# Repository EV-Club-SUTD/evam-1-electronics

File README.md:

# EVAM 1 Electronics Modules

> Design and manufacturing files for the EVAM 1's electrical and CAN bus system

- [x] 🏎️ Automotive Hardware
- [ ] 🛞 Automotive Software
- [ ] 🖥️ Supporting Software and Simulations
- [ ] 📚 Code Library
- [ ] 🛠 Helper Script
- [x] 📖 Documentation / Datasheets
- [ ] ❓ Miscellaneous / Uncategorized

This repository contains the hardware design and manufacturing files for the EVAM 1's electrical system.  

## Directories

* `CANBus 2/Design` - Design files in KiCAD format
    * `/APPS` - Throttle position sensor PCB
    * `/BMS` - Battery Management System PCB
    * `/ECU` - Engine Control Unit PCB
    * `/HUD` - Heads up Display PCB
    * `/MCU_Double` - Motor Control Unit, double motor (for front motors)
    * `/MCU_Single` - Motor Control Unit, single motor (for rear motors)
    * `/SAS` - Steering Angle Sensor, originally meant for torque vectoring. Currently not used
* `CANBus 2/Manufacturing` - Manufacturing files (BOM, placement, and Gerbers)
* `CANBus 2/Electrical Layout` - Electrical layout design files, including block diagrams, to describe the high level overview of the entire electrical system
* `CANBus 2/Harness` - Cable harness design files and pictorial diagrams
* `Datasheets` - All the datasheets for the various components employed in the vehicle

## Documentation

Please refer to EVAM internal OneDrive for further documentation, including specific datasheets on the electrical system components

## Caveats

No known caveats yet

## Known issues

No known issues yet

## Contributing

If you encounter any issues with this repository, please do not hesitate to open an issue.

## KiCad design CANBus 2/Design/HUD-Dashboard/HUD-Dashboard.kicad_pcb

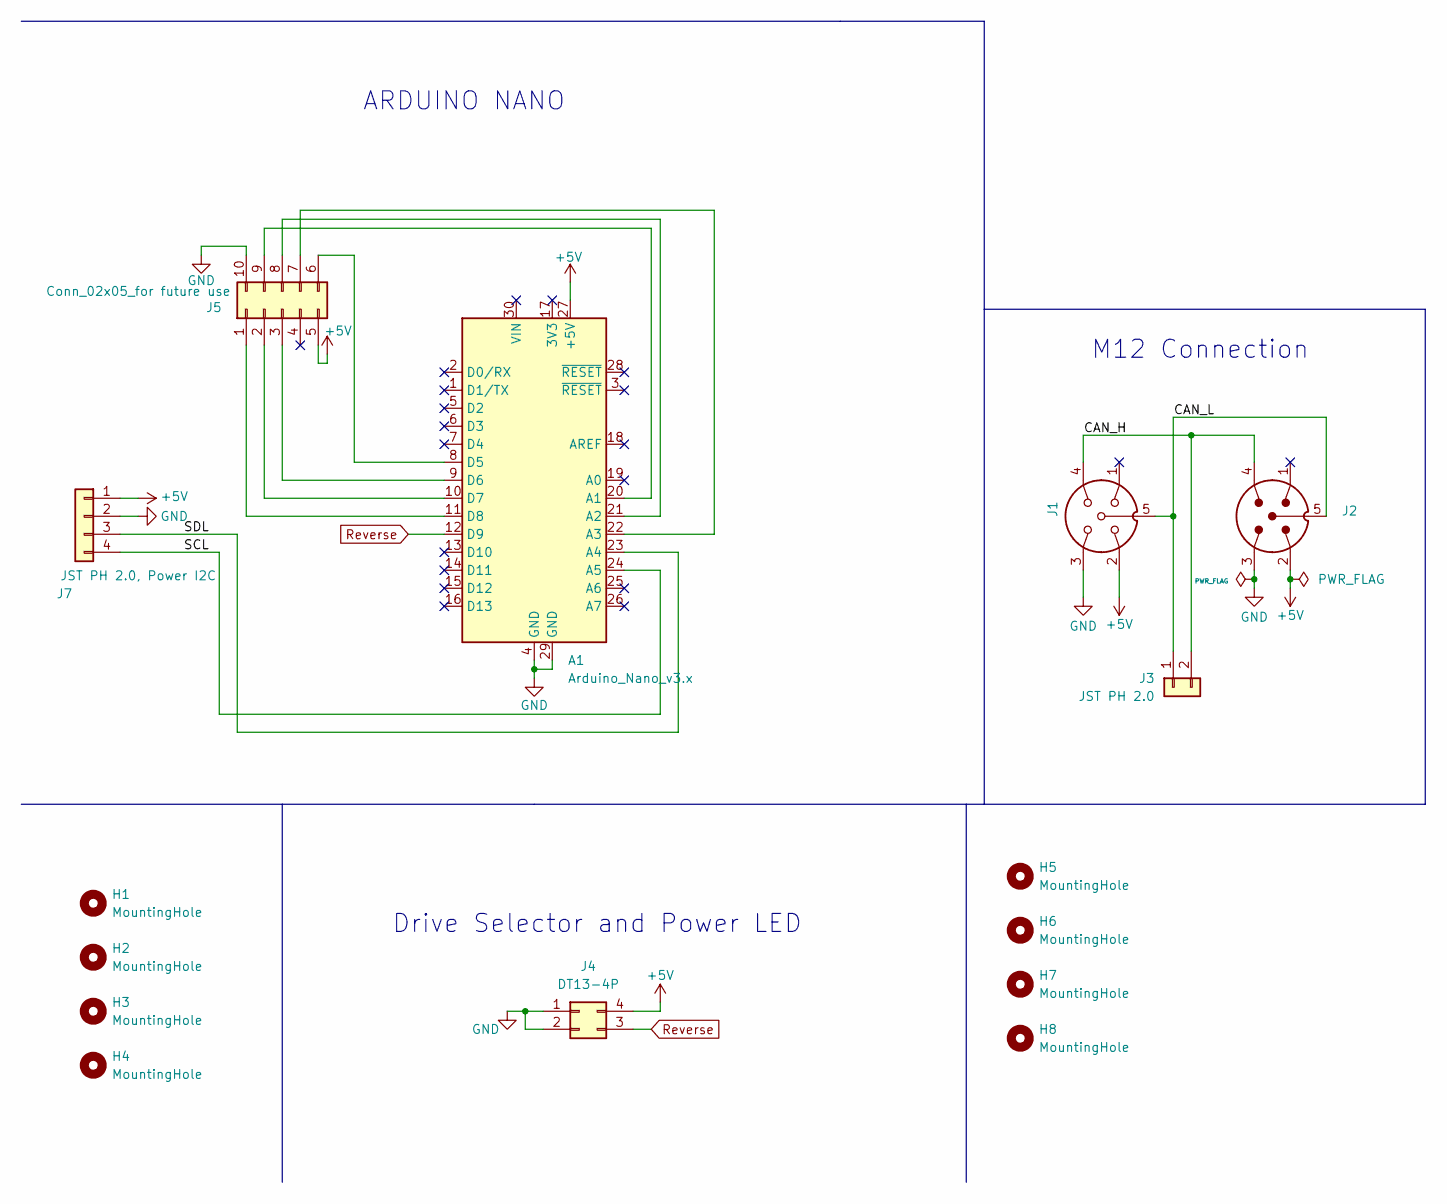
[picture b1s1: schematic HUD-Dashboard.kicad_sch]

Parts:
A1: Arduino_Nano_v3.x; Arduino_Nano
H1, H2, H3, H4, H5, H6, H7, H8: MountingHole; MountingHole_3.2mm_M3_ISO14580
J1: T4145015051-001; M12-S5A-GPL; PARTREV A
J2: TE_T4144015051-000; M12-P5A-GPL; PARTREV A
J3: JST PH 2.0; CONN-TH_2P-P2.00_ZX-HY2.0-2PZZ
J4: DT13-4P; TE_DT13-4P
J5: Conn_02x05_for future use; PinSocket_2x05_P2.54mm_Vertical
J7: JST PH 2.0, Power I2C; CONN-TH_4P-P2.00_ZX-HY2.0-4PZZ

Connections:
+5V: A1.27 (+5V), J1.2, J2.2, J4.4, J5.5, J7.1
/CAN_H: J1.4, J2.4, J3.2
/CAN_L: J1.5, J2.5, J3.1
/SCL: A1.24 (A5), J7.4
/SDL: A1.23 (A4), J7.3
GND: A1.4 (GND), A1.29 (GND), J1.3, J2.3, J4.1, J4.2, J5.10, J7.2
unnamed: A1.20 (A1), J5.9
unnamed: A1.21 (A2), J5.8
unnamed: A1.22 (A3), J5.7
unnamed: A1.8 (D5), J5.6
unnamed: A1.9 (D6), J5.3
unnamed: A1.10 (D7), J5.2
unnamed: A1.11 (D8), J5.1
Reverse: A1.12 (D9), J4.3

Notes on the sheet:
Drive Selector and Power LED
ARDUINO NANO
M12 Connection

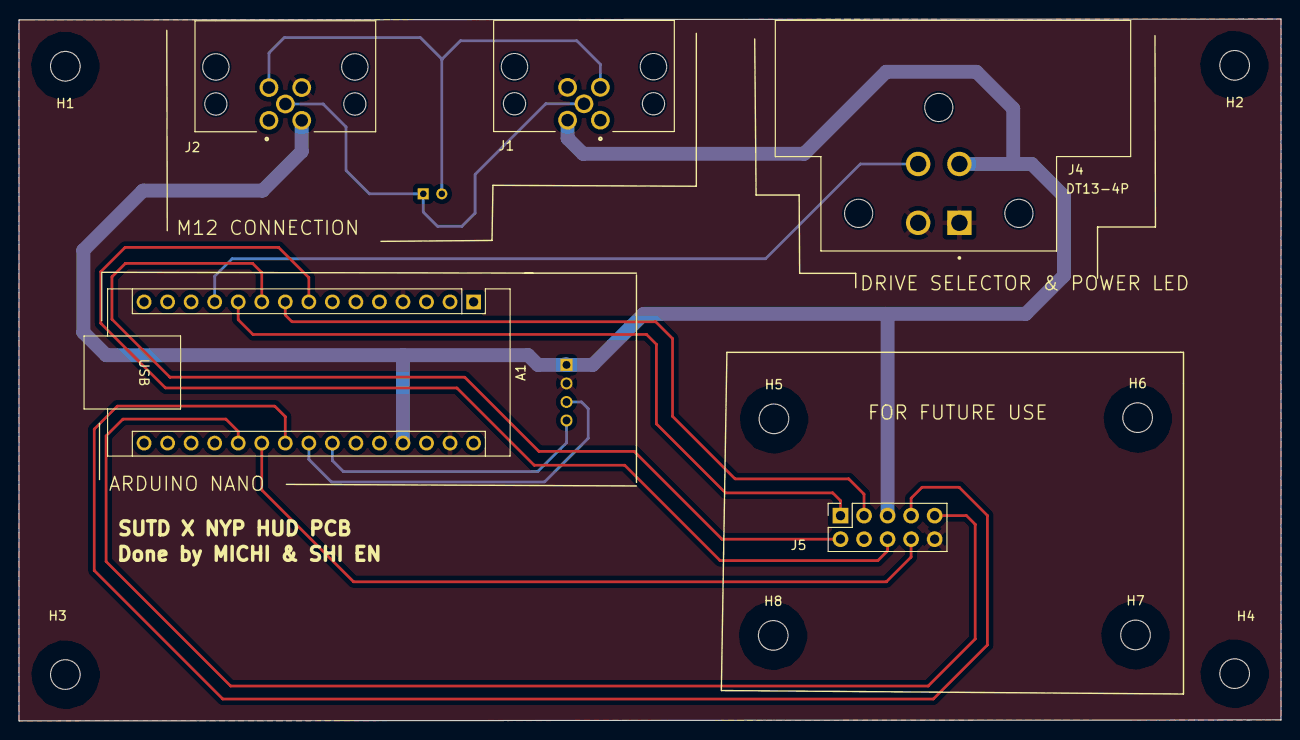
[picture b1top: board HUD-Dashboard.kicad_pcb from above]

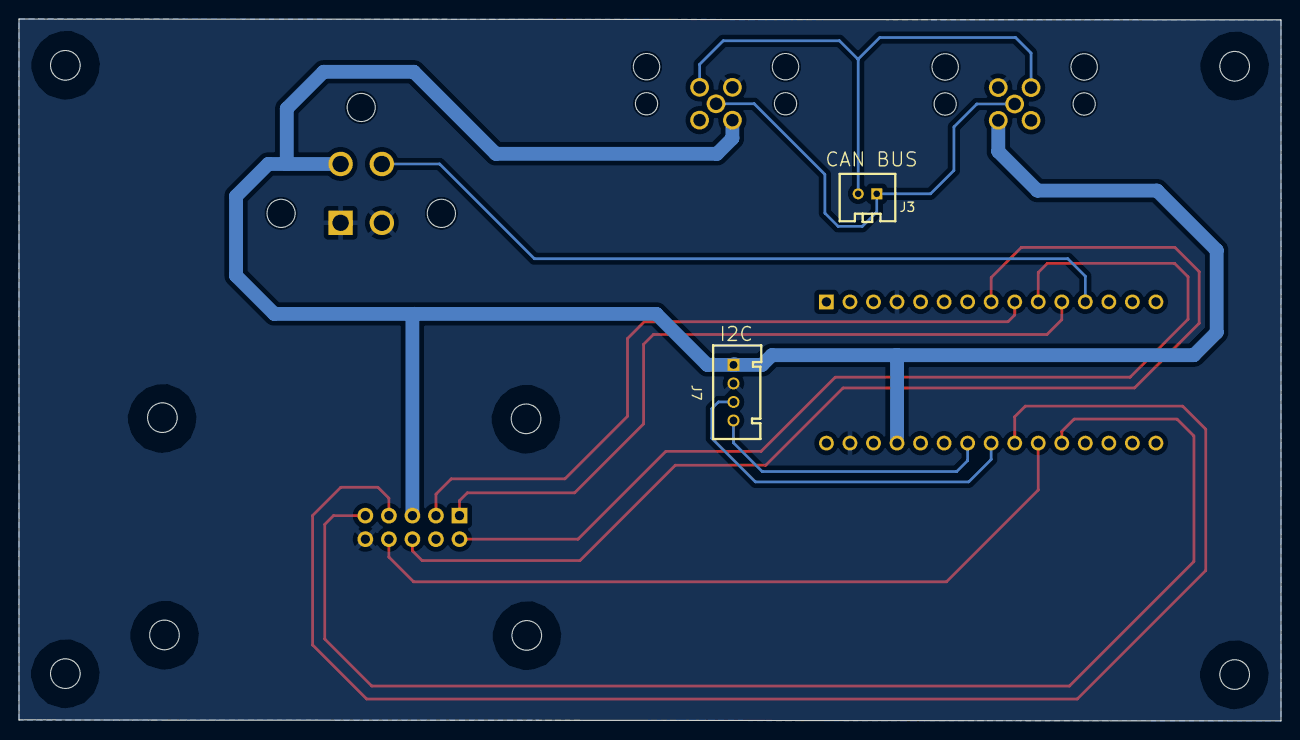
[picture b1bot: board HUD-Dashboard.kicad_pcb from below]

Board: 2 copper layers, 136.2 x 75.8 mm, 15 parts (2 on the bottom side), 14 nets.

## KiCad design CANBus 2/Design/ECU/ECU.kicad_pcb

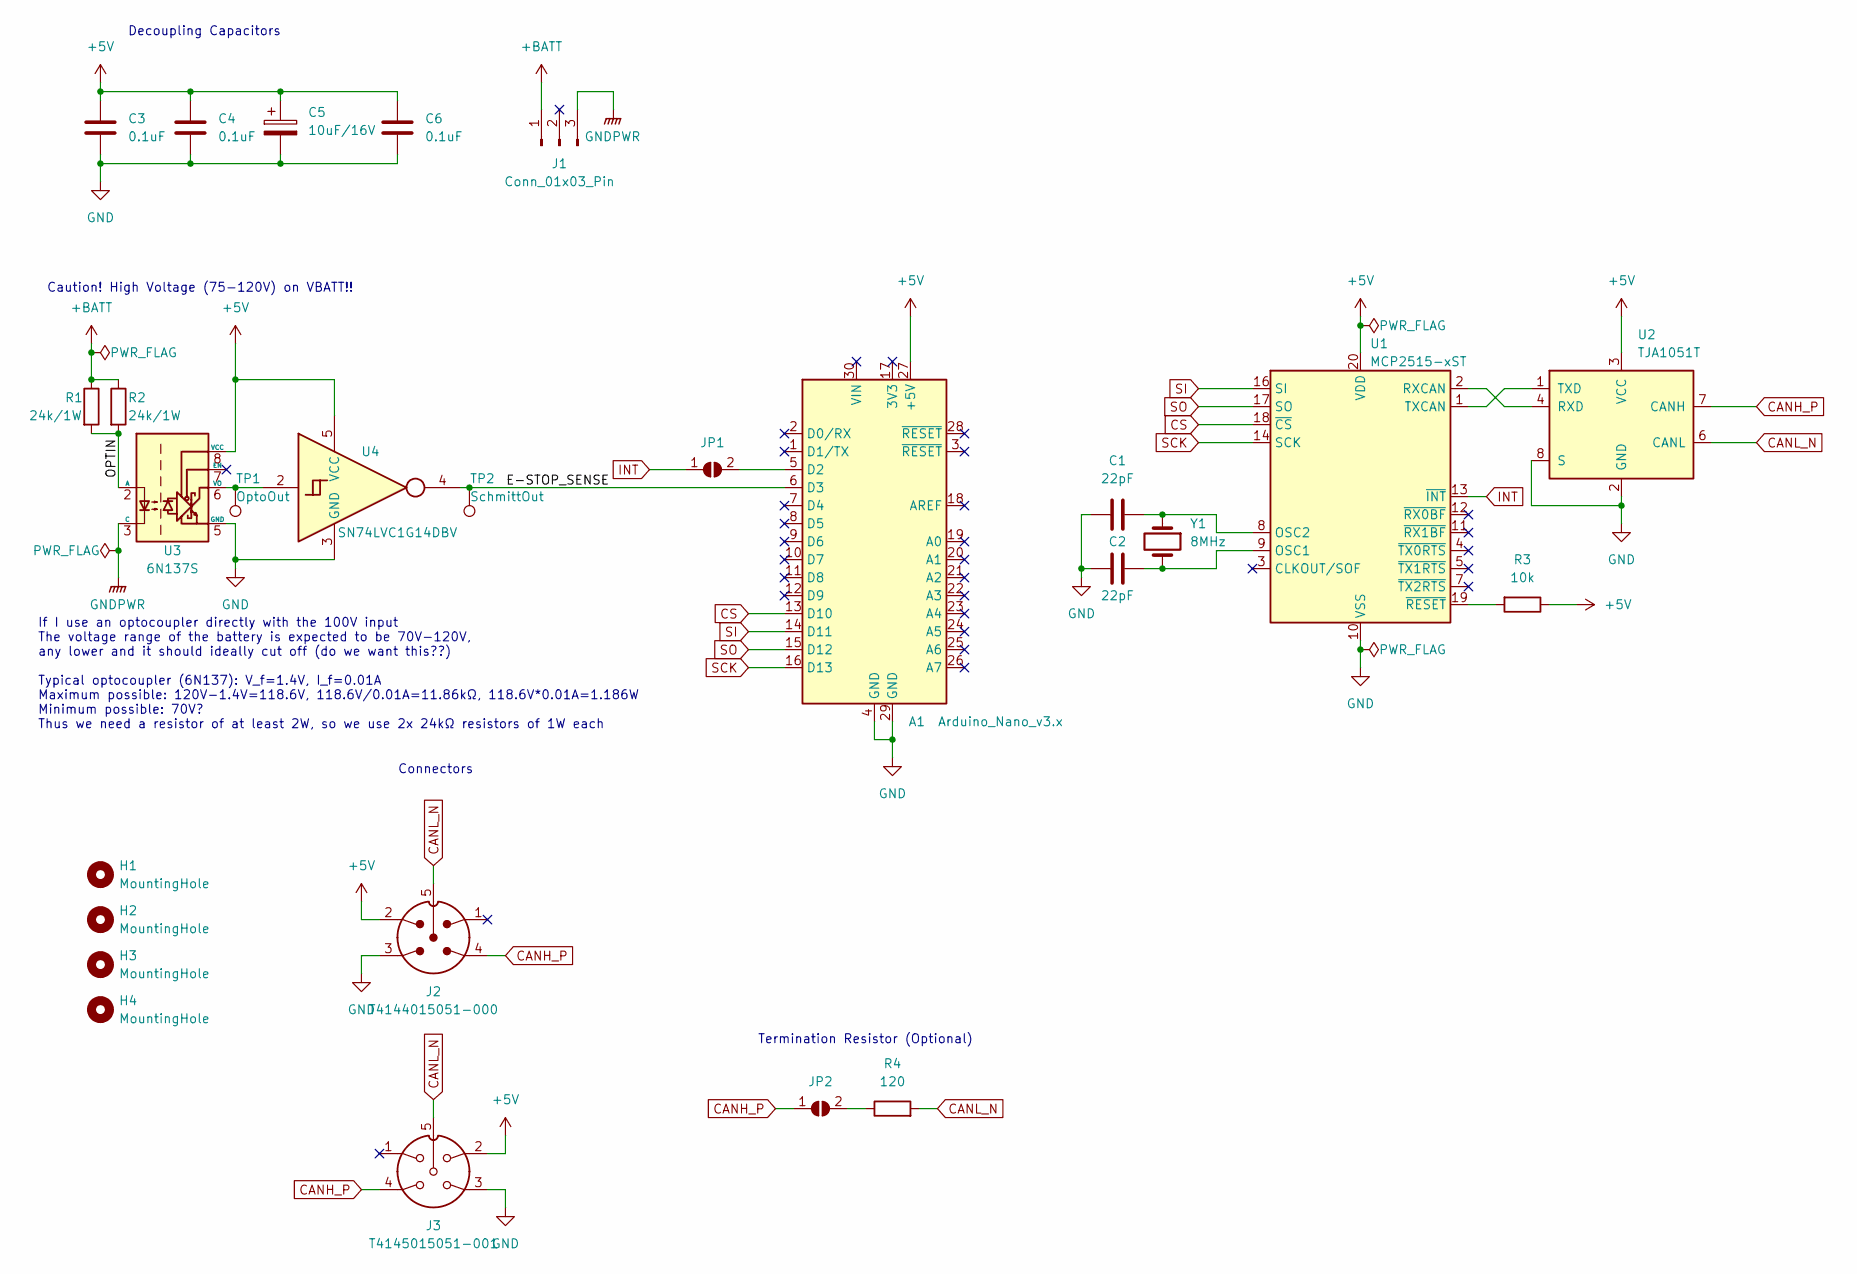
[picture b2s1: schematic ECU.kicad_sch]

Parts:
A1: Arduino_Nano_v3.x; Arduino_Nano
C1, C2: 22pF; C_0603_1608Metric
C3, C4, C6: 0.1uF; C_0603_1608Metric
C5: 10uF/16V; CP_EIA-3216-18_Kemet-A
H1, H2, H3, H4: MountingHole; MountingHole_3.2mm_M3_ISO14580
J1: Conn_01x03_Pin; Molex_KK-254_AE-6410-03A_1x03_P2.54mm_Vertical
J2: T4144015051-000; M12-P5A-GPL; PARTREV A
J3: T4145015051-001; M12-S5A-GPL; PARTREV A
JP1, JP2: Jumper_2_Open; SolderJumper-2_P1.3mm_Open_RoundedPad1.0x1.5mm
R1, R2: 24k/1W; R_2512_6332Metric
R3: 10k; R_0603_1608Metric
R4: 120; R_0603_1608Metric
TP1: OptoOut; TestPoint_Plated_Hole_D2.0mm
TP2: SchmittOut; TestPoint_Plated_Hole_D2.0mm
U1: MCP2515-xST; TSSOP-20_4.4x6.5mm_P0.65mm
U2: TJA1051T; SOIC-8_3.9x4.9mm_P1.27mm
U3: 6N137S; SMDIP-8_W9.53mm
U4: SN74LVC1G14DBV; SOT-23-5
Y1: 8MHz; Crystal_SMD_HC49-SD

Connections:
+5V: A1.27 (+5V), C3.1, C4.1, C5.1, C6.1, J2.2, J3.2, R3.1, U1.20 (VDD), U2.3 (VCC), U3.8 (VCC), U4.5 (VCC)
+BATT: J1.1, R1.1, R2.1
/E-STOP_SENSE: A1.6 (D3), TP2.1, U4.4
/OPTIN: R1.2, R2.2, U3.2 (A)
CANH_P: J2.4, J3.4, JP2.1 (A), U2.7 (CANH)
CANL_N: J2.5, J3.5, R4.2, U2.6 (CANL)
CS: A1.13 (D10), U1.18 (~CS)
GND: A1.4 (GND), A1.29 (GND), C1.1, C2.2, C3.2, C4.2, C5.2, C6.2, J2.3, J3.3, U1.10 (VSS), U2.2 (GND), U2.8 (S), U3.5 (GND), U4.3 (GND)
GNDPWR: J1.3, U3.3 (C)
INT: JP1.1 (A), U1.13 (~INT)
unnamed: A1.5 (D2), JP1.2 (B)
unnamed: JP2.2 (B), R4.1
unnamed: C2.1, U1.9 (OSC1), Y1.2
unnamed: C1.2, U1.8 (OSC2), Y1.1
unnamed: U1.2 (RXCAN), U2.4 (RXD)
unnamed: U1.1 (TXCAN), U2.1 (TXD)
unnamed: R3.2, U1.19 (~RESET)
unnamed: TP1.1, U3.6 (VO), U4.2
SCK: A1.16 (D13), U1.14 (SCK)
SI: A1.14 (D11), U1.16 (SI)
SO: A1.15 (D12), U1.17 (SO)

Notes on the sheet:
Termination Resistor (Optional)
Connectors
If I use an optocoupler directly with the 100V input The voltage range of the battery is expected to be 70V-120V, any lower and it should ideally cut off (do we want this??) Typical optocoupler (6N137): V_f=1.4V, I_f=0.01A Maximum possible: 120V-1.4V=118.6V, 118.6V/0.01A=11.86kΩ, 118.6V*0.01A=1.186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
Caution! High Voltage (75-120V) on VBATT!!
Decoupling Capacitors

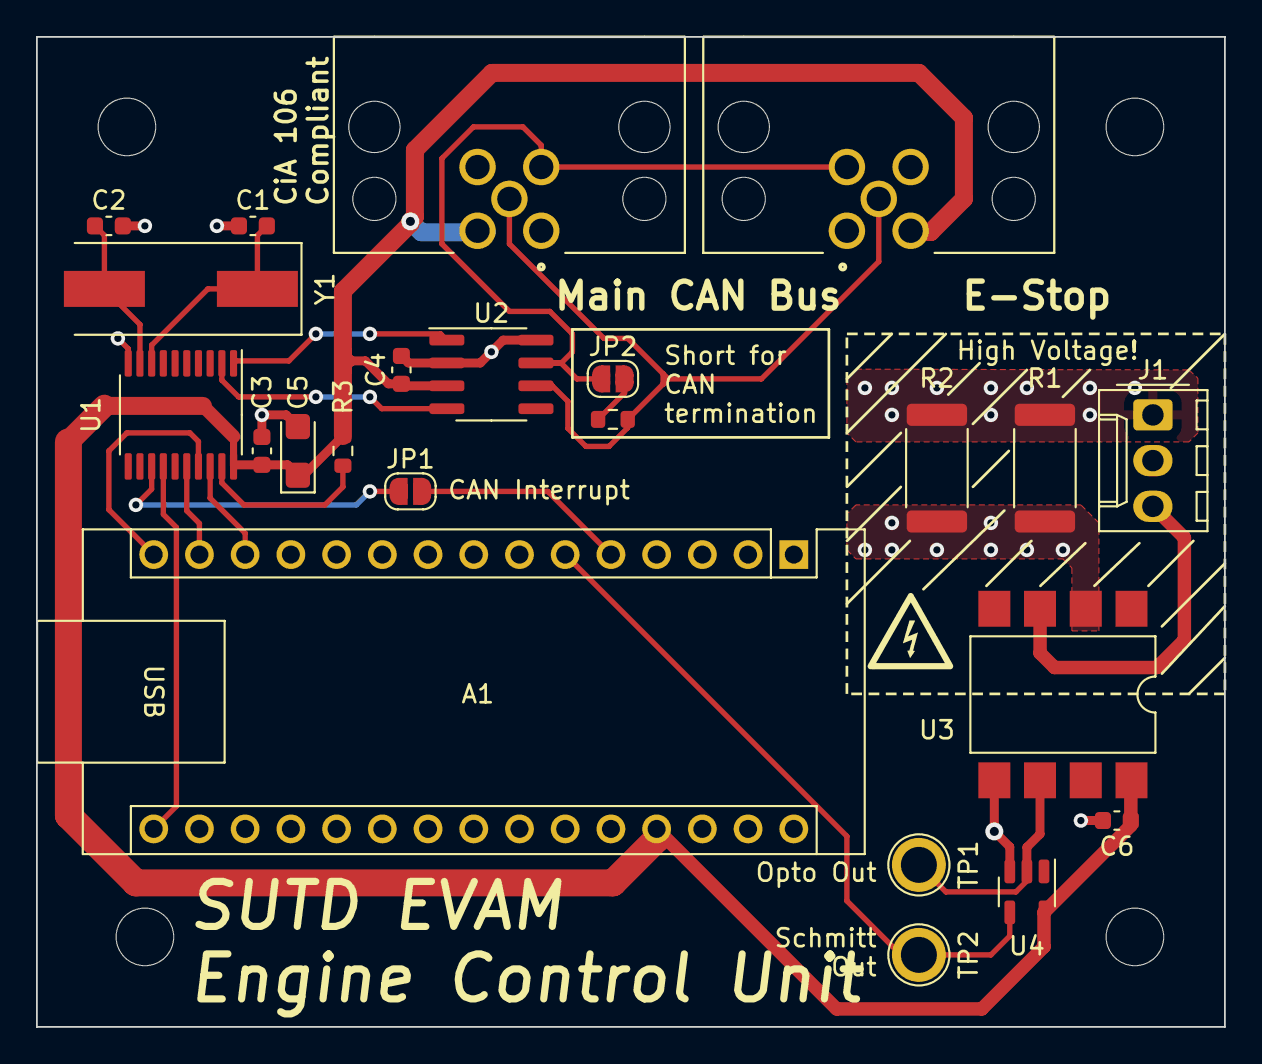
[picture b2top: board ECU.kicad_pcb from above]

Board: 2 copper layers, 66.0 x 55.0 mm, 27 parts (0 on the bottom side), 21 nets.

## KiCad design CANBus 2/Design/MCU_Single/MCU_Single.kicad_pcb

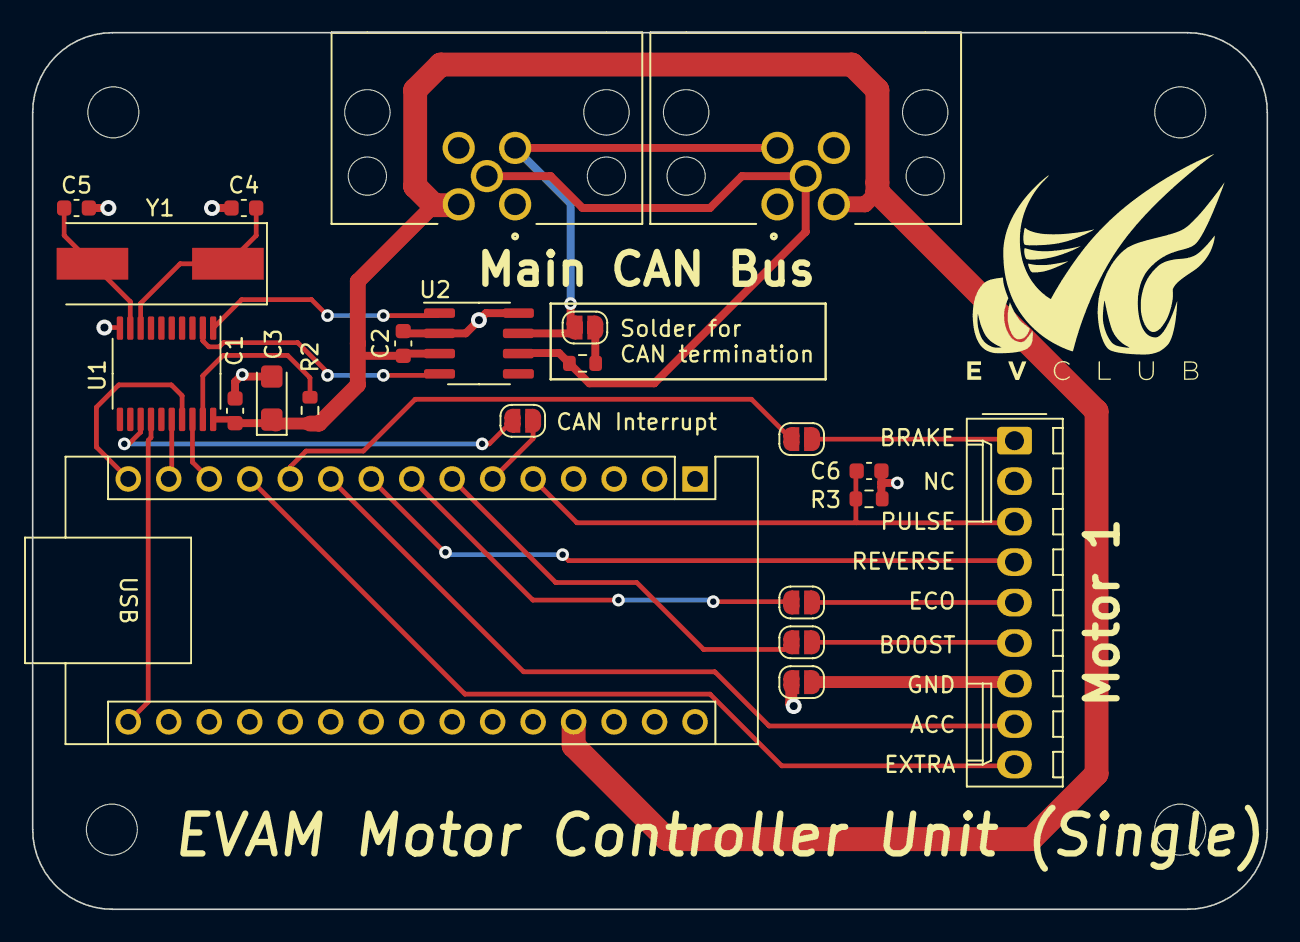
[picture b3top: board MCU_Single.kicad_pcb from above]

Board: 2 copper layers, 77.5 x 55.0 mm, 26 parts (0 on the bottom side), 27 nets.

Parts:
A1: Arduino_Nano_v3.x; Arduino_Nano
C1, C2: 0.1uF; C_0603_1608Metric
C3: 10uF/16V; CP_EIA-3216-18_Kemet-A
C4, C5: 22pF; C_0603_1608Metric
C6: 1nF; C_0603_1608Metric
H1, H2, H3, H4: MountingHole; MountingHole_3.2mm_M3_ISO14580
J1: Conn_01x09_Pin; Molex_KK-254_AE-6410-09A_1x09_P2.54mm_Vertical
J2: T4144015051-000; M12-P5A-GPL
J3: T4145015051-001; M12-S5A-GPL
JP1, JP2, JP3, JP4, JP5, JP6: Jumper_2_Open; SolderJumper-2_P1.3mm_Open_RoundedPad1.0x1.5mm
R1: 120; R_0603_1608Metric
R2: 10k; R_0603_1608Metric
R3: 1M; R_0603_1608Metric
U1: MCP2515-xST; TSSOP-20_4.4x6.5mm_P0.65mm
U2: TJA1051T; SOIC-8_3.9x4.9mm_P1.27mm
Y1: 8MHz; Crystal_SMD_HC49-SD

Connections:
+5V: A1.27 (+5V), C1.1, C2.1, C3.1, J2.2, J3.2, R2.1, U1.20 (VDD), U2.3 (VCC)
ACC_1: A1.10 (D7), J1.8
BOOST: A1.7 (D4), JP4.2 (B)
CANH_P: J2.4, J3.4, JP2.1 (A), U2.7 (CANH)
CANL_N: J2.5, J3.5, R1.2, U2.6 (CANL)
CS: A1.13 (D10), U1.18 (~CS)
ECO: A1.8 (D5), JP5.2 (B)
EXTRA_1: A1.12 (D9), J1.9
GND: A1.4 (GND), A1.29 (GND), C1.2, C2.2, C3.2, C4.1, C5.2, C6.2, J2.3, J3.3, JP3.2 (B), R3.2, U1.10 (VSS), U2.2 (GND), U2.8 (S)
INT: JP1.1 (A), U1.13 (~INT)
LOCK: A1.11 (D8), JP6.2 (B)
unnamed: A1.6 (D3), JP1.2 (B)
unnamed: J1.1, JP6.1 (A)
unnamed: J1.5, JP5.1 (A)
unnamed: J1.6, JP4.1 (A)
unnamed: J1.7, JP3.1 (A)
unnamed: JP2.2 (B), R1.1
unnamed: C5.1, U1.9 (OSC1), Y1.2
unnamed: C4.2, U1.8 (OSC2), Y1.1
unnamed: U1.2 (RXCAN), U2.4 (RXD)
unnamed: U1.1 (TXCAN), U2.1 (TXD)
unnamed: R2.2, U1.19 (~RESET)
PULSE: A1.5 (D2), C6.1, J1.3, R3.1
REVERSE: A1.9 (D6), J1.4
SCK: A1.16 (D13), U1.14 (SCK)
SI: A1.14 (D11), U1.16 (SI)
SO: A1.15 (D12), U1.17 (SO)

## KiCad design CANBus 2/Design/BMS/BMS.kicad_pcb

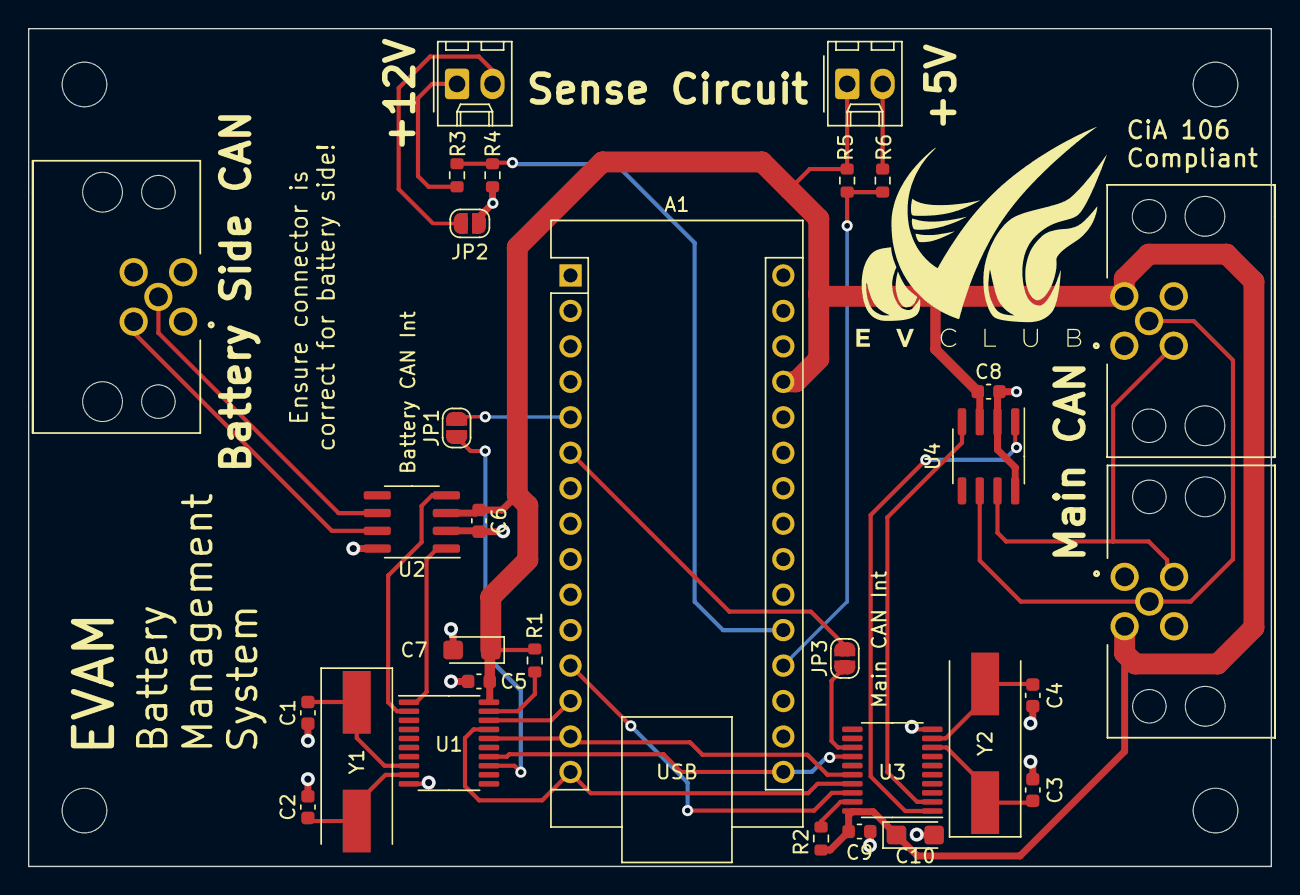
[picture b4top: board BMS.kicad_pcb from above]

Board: 2 copper layers, 89.0 x 60.0 mm, 35 parts (0 on the bottom side), 29 nets.

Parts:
A1: Arduino_Nano_v3.x; Arduino_Nano
C1, C2, C3, C4: 22pF; C_0603_1608Metric
C5, C6, C8, C9: 0.1uF; C_0603_1608Metric
C7, C10: 10uF/16V; CP_EIA-3216-18_Kemet-A
H1, H2, H3, H4: MountingHole; MountingHole_3.2mm_M3_ISO14580
J1, J3: T4144015051-000; M12-P5A-GPL
J2: T4145015051-001; M12-S5A-GPL
J4, J5: Conn_01x02_Pin; Molex_KK-254_AE-6410-02A_1x02_P2.54mm_Vertical
JP1, JP2, JP3: SolderJumper_2_Open; SolderJumper-2_P1.3mm_Open_RoundedPad1.0x1.5mm
R1, R2, R3, R5, R6: 10k; R_0603_1608Metric
R4: 2.7k; R_0603_1608Metric
U1, U3: MCP2515-xST; TSSOP-20_4.4x6.5mm_P0.65mm
U2, U4: TJA1051T; SOIC-8_3.9x4.9mm_P1.27mm
Y1, Y2: 8MHz; Crystal_SMD_HC49-SD

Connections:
5V_Sense: A1.19 (A0), R5.2, R6.1
12V_Sense: A1.20 (A1), R3.2, R4.1
+5V: A1.27 (+5V), C5.1, C6.1, C7.1, C8.1, C9.1, C10.1, J1.2, J2.2, J4.1, R1.1, R2.1, R5.1, U1.20 (VDD), U2.3 (VCC), U3.20 (VDD), U4.3 (VCC)
+12V: J5.1, R3.1
CANH_P: J1.4, J2.4, U4.7 (CANH)
CANH_P_BATT: J3.4, U2.7 (CANH)
CANL_N: J1.5, J2.5, U4.6 (CANL)
CANL_N_BATT: J3.5, U2.6 (CANL)
CS_BATT: A1.13 (D10), U1.18 (~CS)
CS_CAR: A1.12 (D9), U3.18 (~CS)
GND: A1.4 (GND), A1.29 (GND), C1.1, C2.2, C3.1, C4.2, C5.2, C6.2, C7.2, C8.2, C9.2, C10.2, J1.3, J2.3, J3.3, J4.2, JP2.2 (B), R4.2, R6.2, U1.10 (VSS), U2.2 (GND), U2.8 (S), U3.10 (VSS), U4.2 (GND), U4.8 (S)
INT_BATT: JP1.1 (A), U1.13 (~INT)
INT_CAR: JP3.1 (A), U3.13 (~INT)
unnamed: A1.5 (D2), JP1.2 (B)
unnamed: A1.6 (D3), JP3.2 (B)
unnamed: J5.2, JP2.1 (A)
unnamed: C2.1, U1.9 (OSC1), Y1.2
unnamed: C1.2, U1.8 (OSC2), Y1.1
unnamed: U1.2 (RXCAN), U2.4 (RXD)
unnamed: U1.1 (TXCAN), U2.1 (TXD)
unnamed: R1.2, U1.19 (~RESET)
unnamed: C4.1, U3.9 (OSC1), Y2.2
unnamed: C3.2, U3.8 (OSC2), Y2.1
unnamed: U3.2 (RXCAN), U4.4 (RXD)
unnamed: U3.1 (TXCAN), U4.1 (TXD)
unnamed: R2.2, U3.19 (~RESET)
SCK: A1.16 (D13), U1.14 (SCK), U3.14 (SCK)
SI: A1.14 (D11), U1.16 (SI), U3.16 (SI)
SO: A1.15 (D12), U1.17 (SO), U3.17 (SO)

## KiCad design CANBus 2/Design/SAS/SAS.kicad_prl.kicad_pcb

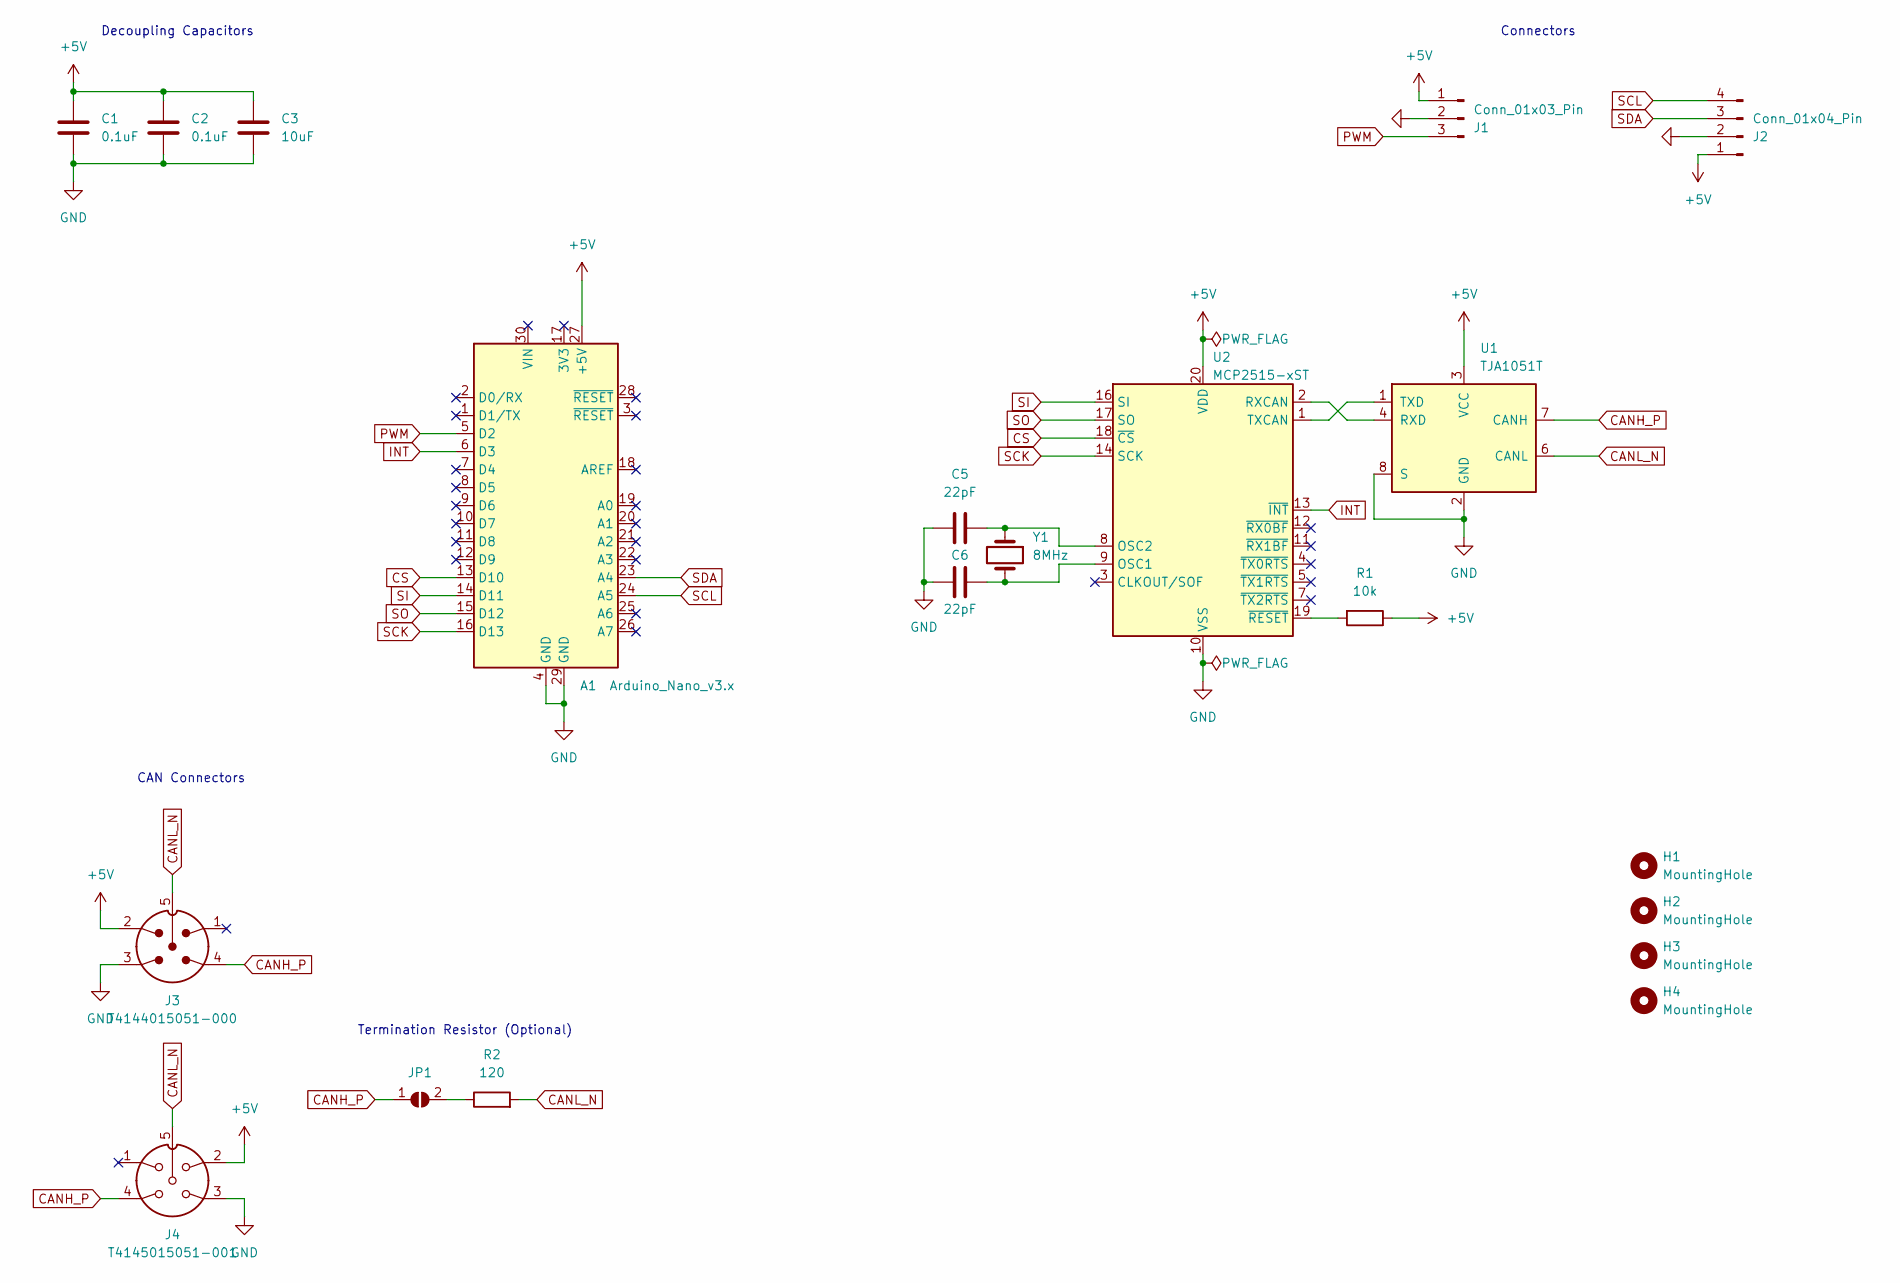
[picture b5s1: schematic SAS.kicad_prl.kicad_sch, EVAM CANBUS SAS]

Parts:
A1: Arduino_Nano_v3.x; Arduino_Nano
C1, C2: 0.1uF; C_0603_1608Metric
C3: 10uF; C_0805_2012Metric
C5, C6: 22pF; C_0603_1608Metric
H1, H2, H3, H4: MountingHole; MountingHole_3.2mm_M3_ISO14580
J1: Conn_01x03_Pin; Molex_KK-254_AE-6410-03A_1x03_P2.54mm_Vertical
J2: Conn_01x04_Pin; Molex_KK-254_AE-6410-04A_1x04_P2.54mm_Vertical
J3: T4144015051-000; M12-P5A-GPL; PARTREV A
J4: T4145015051-001; M12-S5A-GPL; PARTREV A
JP1: Jumper_2_Open; SolderJumper-2_P1.3mm_Open_RoundedPad1.0x1.5mm
R1: 10k; R_0603_1608Metric
R2: 120; R_0603_1608Metric
U1: TJA1051T; SOIC-8_3.9x4.9mm_P1.27mm
U2: MCP2515-xST; TSSOP-20_4.4x6.5mm_P0.65mm
Y1: 8MHz; Crystal_SMD_HC49-SD

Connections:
+5V: A1.27 (+5V), C1.1, C2.1, C3.1, J1.1, J2.1, J3.2, J4.2, R1.1, U1.3 (VCC), U2.20 (VDD)
CANH_P: J3.4, J4.4, JP1.1 (A), U1.7 (CANH)
CANL_N: J3.5, J4.5, R2.2, U1.6 (CANL)
CS: A1.13 (D10), U2.18 (~CS)
GND: A1.4 (GND), A1.29 (GND), C1.2, C2.2, C3.2, C5.1, C6.2, J1.2, J2.2, J3.3, J4.3, U1.2 (GND), U1.8 (S), U2.10 (VSS)
INT: A1.6 (D3), U2.13 (~INT)
unnamed: JP1.2 (B), R2.1
unnamed: U1.4 (RXD), U2.2 (RXCAN)
unnamed: U1.1 (TXD), U2.1 (TXCAN)
unnamed: C6.1, U2.9 (OSC1), Y1.2
unnamed: C5.2, U2.8 (OSC2), Y1.1
unnamed: R1.2, U2.19 (~RESET)
PWM: A1.5 (D2), J1.3
SCK: A1.16 (D13), U2.14 (SCK)
SCL: A1.24 (A5), J2.4
SDA: A1.23 (A4), J2.3
SI: A1.14 (D11), U2.16 (SI)
SO: A1.15 (D12), U2.17 (SO)

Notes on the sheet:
Decoupling Capacitors
CAN Connectors
Termination Resistor (Optional)
Connectors

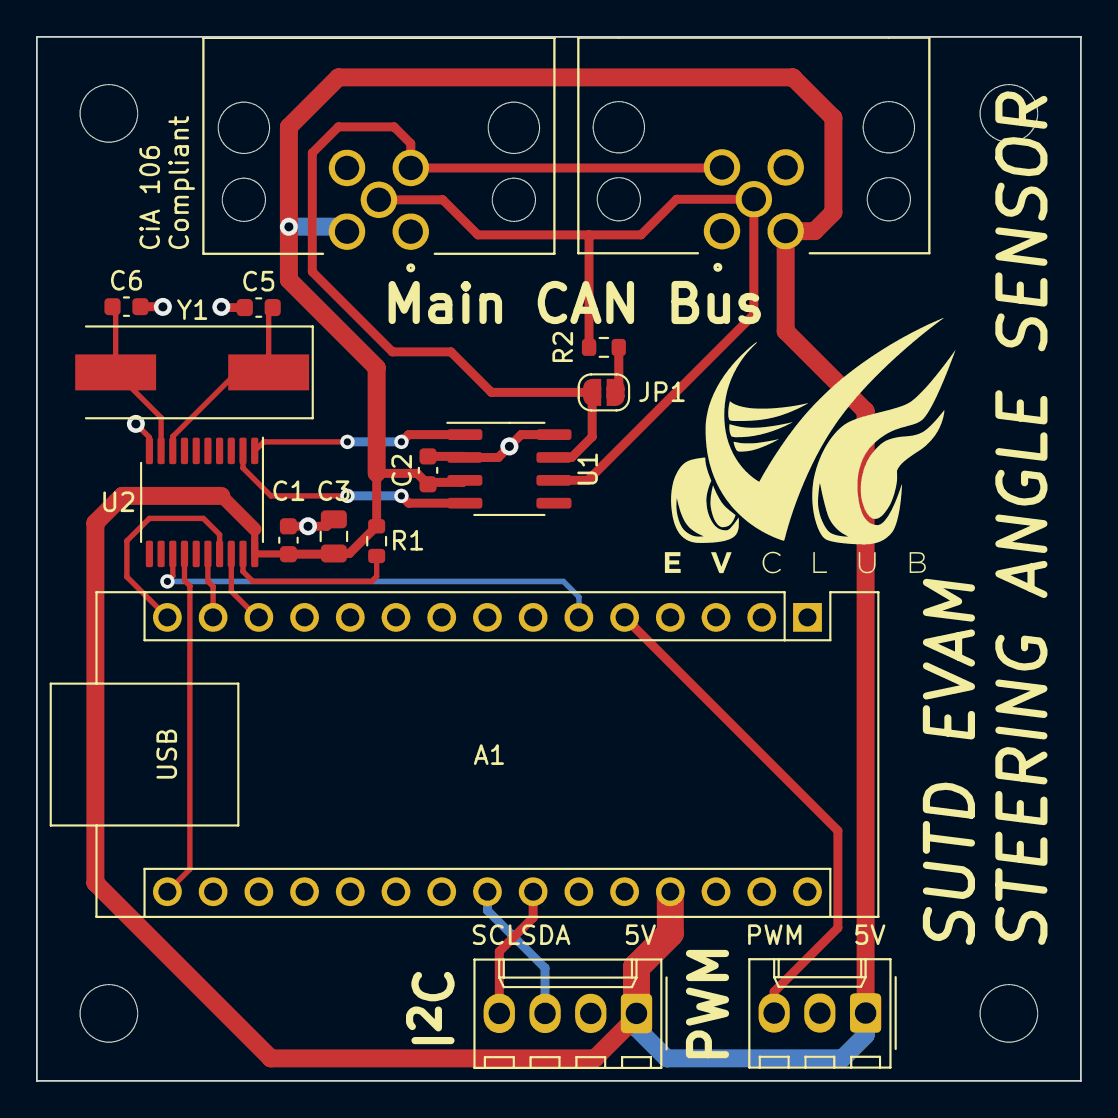
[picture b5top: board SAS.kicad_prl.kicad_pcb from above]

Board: 2 copper layers, 58.0 x 58.0 mm, 20 parts (0 on the bottom side), 18 nets.

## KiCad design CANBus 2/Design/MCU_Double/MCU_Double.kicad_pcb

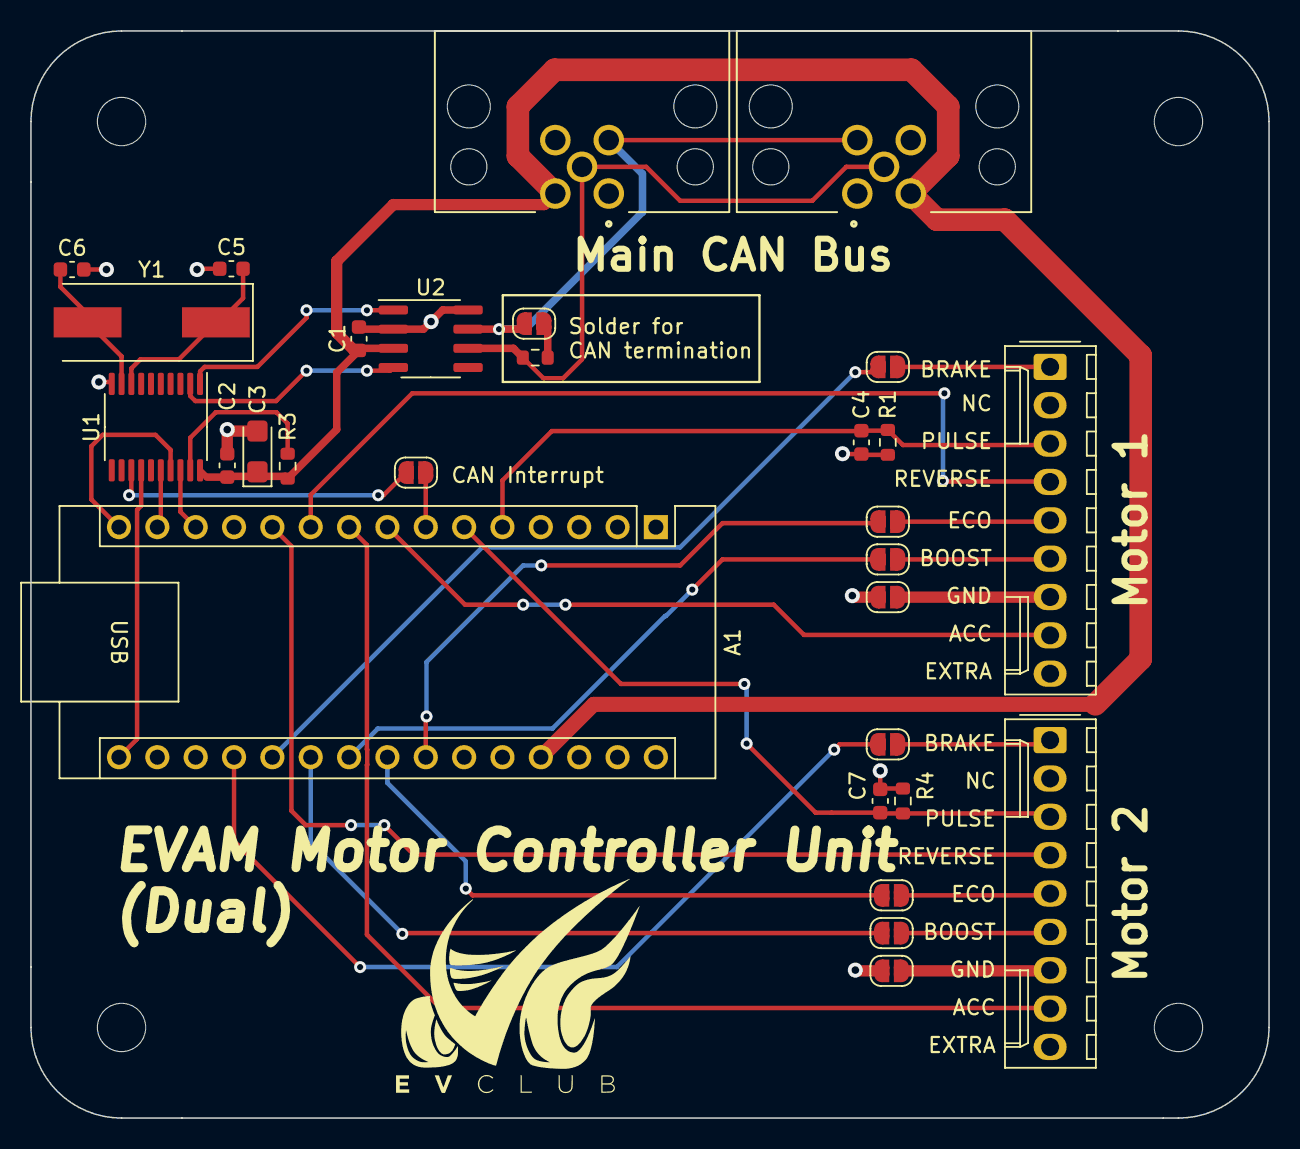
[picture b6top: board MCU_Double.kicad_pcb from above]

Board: 2 copper layers, 82.0 x 72.0 mm, 33 parts (0 on the bottom side), 36 nets.

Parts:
A1: Arduino_Nano_v3.x; Arduino_Nano
C1, C2: 0.1uF; C_0603_1608Metric
C3: 10uF/16V; CP_EIA-3216-18_Kemet-A
C4, C7: 1nF; C_0603_1608Metric
C5, C6: 22pF; C_0603_1608Metric
H1, H2, H3, H4: MountingHole; MountingHole_3.2mm_M3_ISO14580
J1, J4: Conn_01x09_Pin; Molex_KK-254_AE-6410-09A_1x09_P2.54mm_Vertical
J2: T4144015051-000; M12-P5A-GPL
J3: T4145015051-001; M12-S5A-GPL
JP1, JP2, JP3, JP4, JP5, JP6, JP7, JP8, JP9, JP10: Jumper_2_Open; SolderJumper-2_P1.3mm_Open_RoundedPad1.0x1.5mm
R1, R4: 1M; R_0603_1608Metric
R2: 120; R_0603_1608Metric
R3: 10k; R_0603_1608Metric
U1: MCP2515-xST; TSSOP-20_4.4x6.5mm_P0.65mm
U2: TJA1051T; SOIC-8_3.9x4.9mm_P1.27mm
Y1: 8MHz; Crystal_SMD_HC49-SD

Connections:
+5V: A1.27 (+5V), C1.1, C2.1, C3.1, J2.2, J3.2, R3.1, U1.20 (VDD), U2.3 (VCC)
ACC_1: A1.8 (D5), J1.8
ACC_2: A1.9 (D6), J4.8
BOOST: A1.22 (A3), JP3.2 (B)
BOOST2: A1.21 (A2), JP9.2 (B)
CANH_P: J2.4, J3.4, JP6.1 (A), U2.7 (CANH)
CANL_N: J2.5, J3.5, R2.2, U2.6 (CANL)
CS: A1.13 (D10), U1.18 (~CS)
ECO: A1.24 (A5), JP4.2 (B)
ECO2: A1.23 (A4), JP10.2 (B)
GND: A1.4 (GND), A1.29 (GND), C1.2, C2.2, C3.2, C4.2, C5.1, C6.2, C7.2, J2.3, J3.3, JP1.2 (B), JP7.2 (B), R1.2, R4.2, U1.10 (VSS), U2.2 (GND), U2.8 (S)
INT: JP5.1 (A), U1.13 (~INT)
LOCK: A1.20 (A1), JP2.2 (B)
LOCK2: A1.19 (A0), JP8.2 (B)
unnamed: A1.7 (D4), JP5.2 (B)
unnamed: J1.1, JP2.1 (A)
unnamed: J1.5, JP4.1 (A)
unnamed: J1.6, JP3.1 (A)
unnamed: J1.7, JP1.1 (A)
unnamed: J4.1, JP8.1 (A)
unnamed: J4.5, JP10.1 (A)
unnamed: J4.6, JP9.1 (A)
unnamed: J4.7, JP7.1 (A)
unnamed: JP6.2 (B), R2.1
unnamed: C6.1, U1.9 (OSC1), Y1.2
unnamed: C5.2, U1.8 (OSC2), Y1.1
unnamed: U1.2 (RXCAN), U2.4 (RXD)
unnamed: U1.1 (TXCAN), U2.1 (TXD)
unnamed: R3.2, U1.19 (~RESET)
PULSE: A1.5 (D2), C4.1, J1.3, R1.1
PULSE2: A1.6 (D3), C7.1, J4.3, R4.1
REVERSE: A1.10 (D7), J1.4
REVERSE2: A1.11 (D8), J4.4
SCK: A1.16 (D13), U1.14 (SCK)
SI: A1.14 (D11), U1.16 (SI)
SO: A1.15 (D12), U1.17 (SO)
